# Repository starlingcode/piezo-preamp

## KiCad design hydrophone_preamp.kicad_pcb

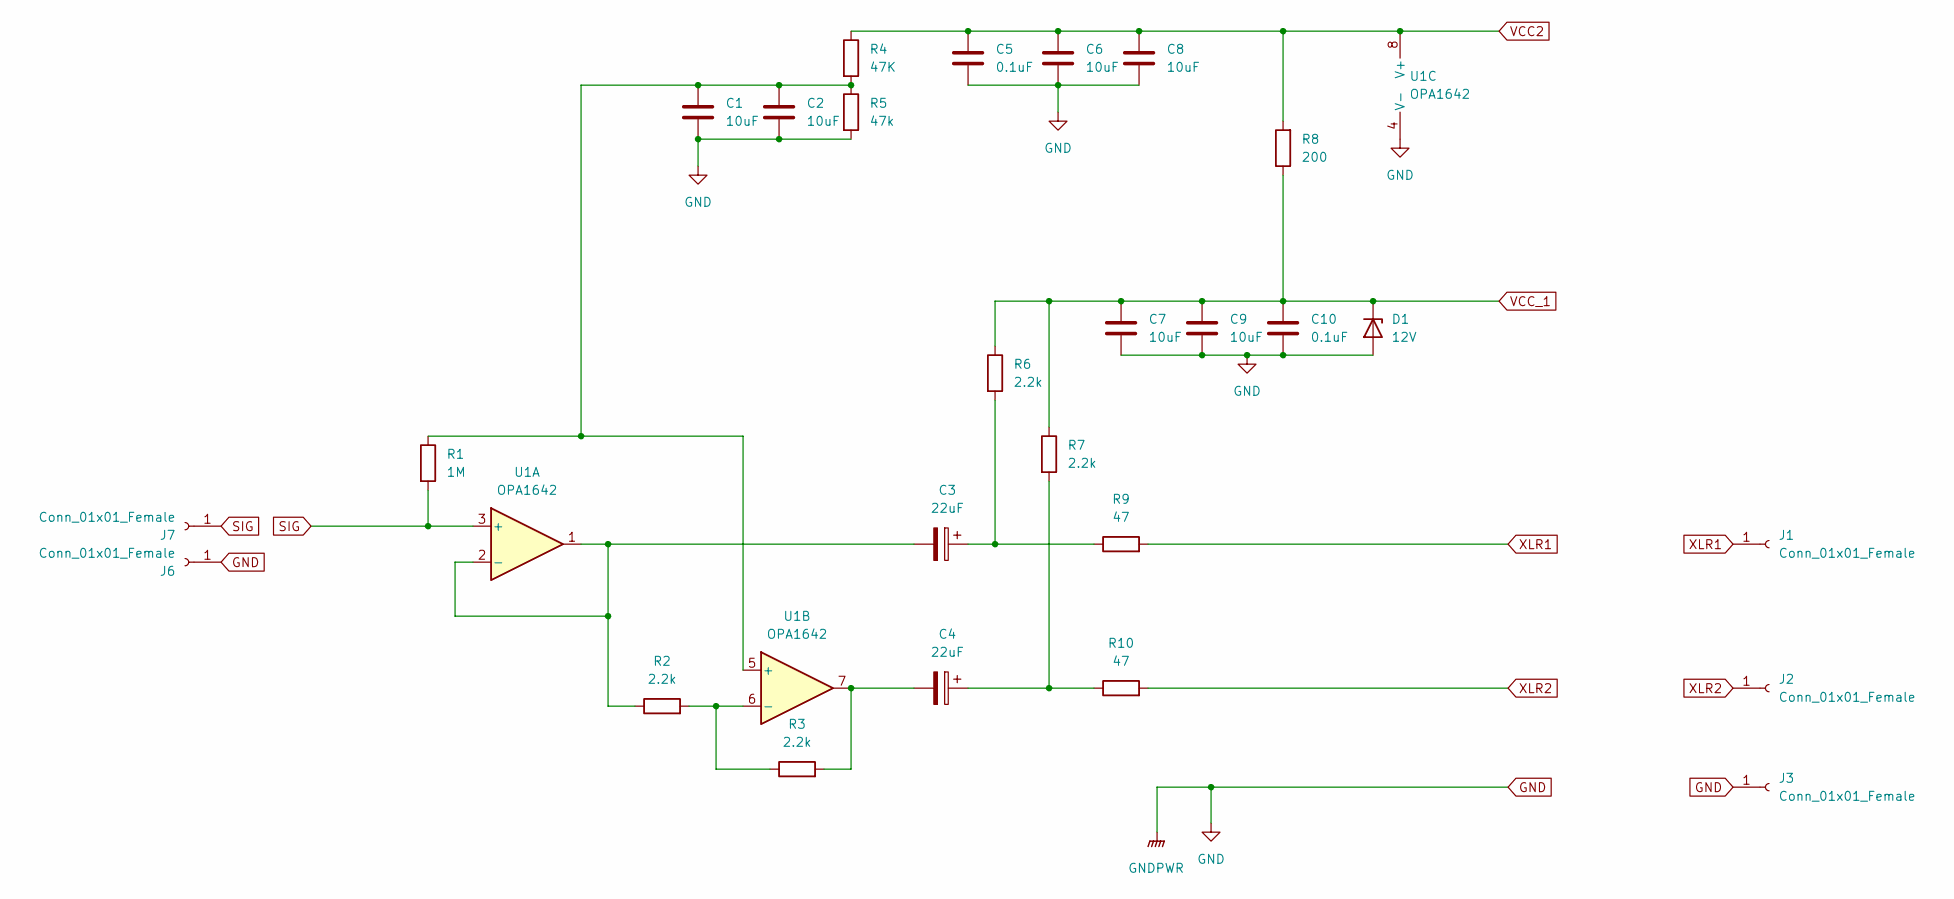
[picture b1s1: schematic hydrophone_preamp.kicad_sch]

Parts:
C1, C2, C6, C7, C8, C9: 10uF; C_1206_3216Metric; JLC C77093
C3, C4: 22uF; CP_Elec_6.3x3.9; JLC C2761583
C5, C10: 0.1uF; C_0603_1608Metric; JLC C14663
D1: 12V; D_SOD-323F; JLC C84980
J1, J2, J3: Conn_01x01_Female; SolderWire-1.5sqmm_1x01_D1.7mm_OD3.9mm
J6, J7: Conn_01x01_Female; SolderWire-0.5sqmm_1x01_D0.9mm_OD2.1mm
R1: 1M; R_0603_1608Metric
R2, R3, R6, R7: 2.2k; R_0603_1608Metric
R4: 47K; R_0603_1608Metric
R5: 47k; R_0603_1608Metric
R8: 200; R_0603_1608Metric
R9, R10: 47; R_0603_1608Metric
U1: OPA1642; SOIC-8_3.9x4.9mm_P1.27mm

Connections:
GND: C1.2, C2.2, C5.2, C6.2, C7.2, C8.2, C9.2, C10.2, D1.2 (A), J3.1, J6.1, R5.2, U1.4 (V-)
unnamed: C1.1, C2.1, R1.1, R4.2, R5.1, U1.5 (+)
unnamed: C3.1, R6.2, R9.1
unnamed: C3.2, R2.1, U1.1, U1.2 (-)
unnamed: C4.1, R7.2, R10.1
unnamed: C4.2, R3.2, U1.7
unnamed: R2.2, R3.1, U1.6 (-)
SIG: J7.1, R1.2, U1.3 (+)
VCC2: C5.1, C6.1, C8.1, R4.1, R8.2, U1.8 (V+)
VCC_1: C7.1, C9.1, C10.1, D1.1 (K), R6.1, R7.1, R8.1
XLR1: J1.1, R9.2
XLR2: J2.1, R10.2

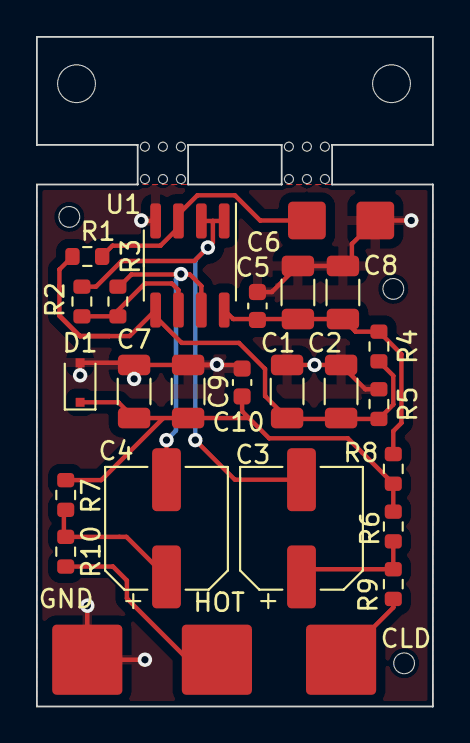
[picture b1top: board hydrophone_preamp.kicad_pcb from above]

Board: 2 copper layers, 22.0 x 37.2 mm, 27 parts (0 on the bottom side), 12 nets.
